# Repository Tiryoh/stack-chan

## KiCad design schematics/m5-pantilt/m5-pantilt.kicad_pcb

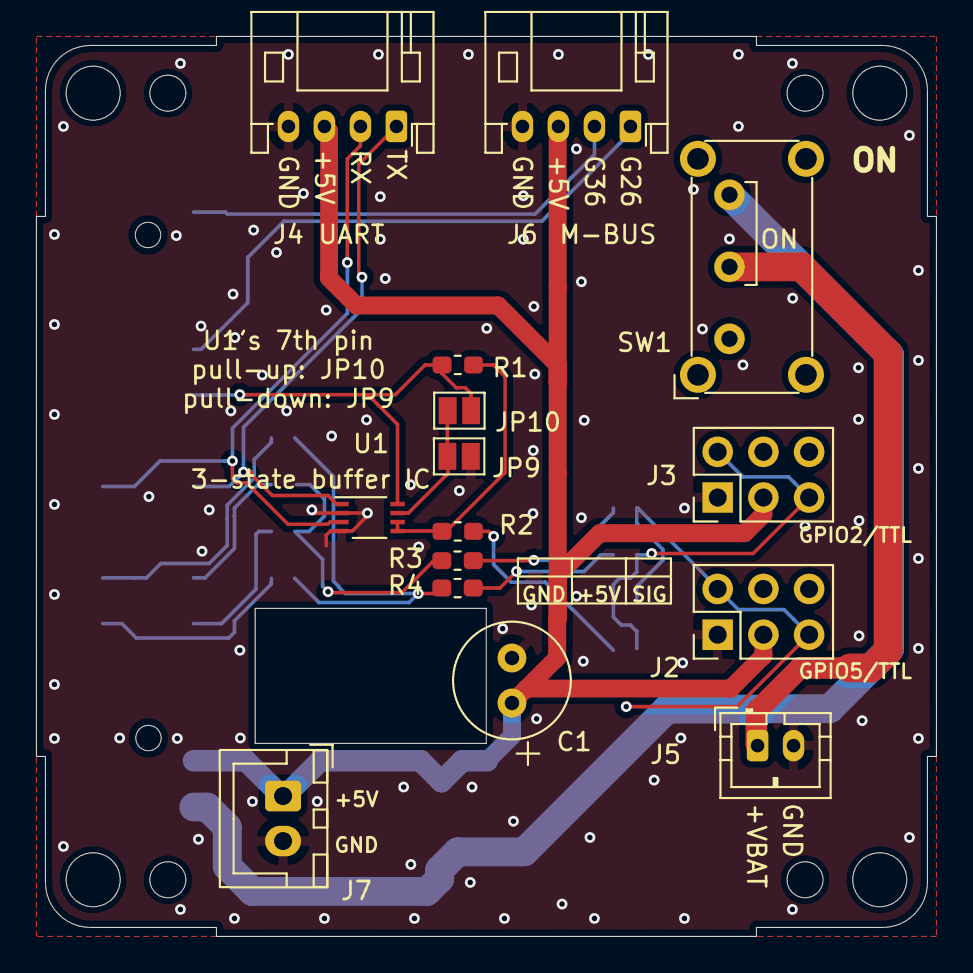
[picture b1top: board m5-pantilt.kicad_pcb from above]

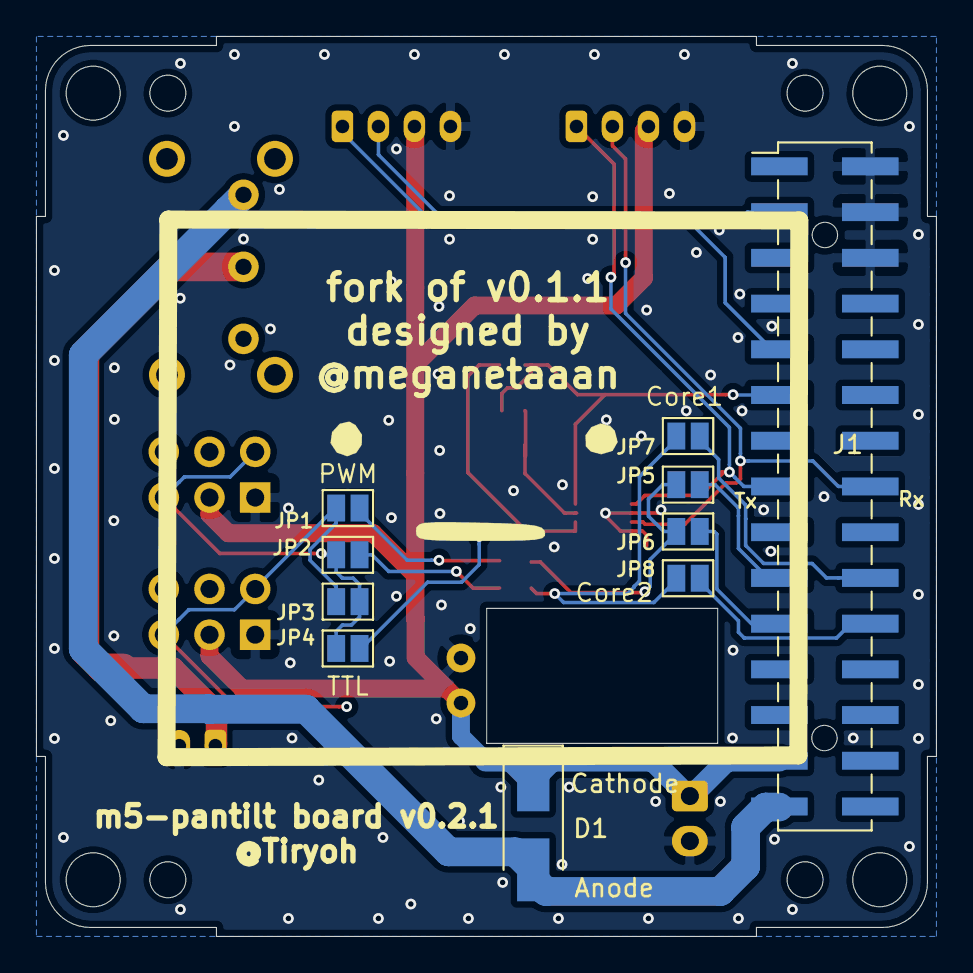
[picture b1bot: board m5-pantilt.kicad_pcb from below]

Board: 2 copper layers, 50.0 x 50.0 mm, 30 parts (11 on the bottom side), 22 nets.

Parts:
C1: 100u; C_Radial_D6.3mm_H11.0mm_P2.50mm
D1: D; D_SMA_Handsoldering
Hole1, Hole2, Hole3, Hole4: mountinghole_M2_M3
J1: Conn_02x15_Odd_Even; PinHeader_2x15_P2.54mm_Vertical_SMD
J2, J3: Conn_02x03_Odd_Even; PinHeader_2x03_P2.54mm_Vertical
J4, J6: Conn_01x04; JST_PH_S4B-PH-K_1x04_P2.00mm_Horizontal
J5: BAT; JST_PH_B2B-PH-K_1x02_P2.00mm_Vertical
J7: 5V_POWER; JST_XH_B2B-XH-A_1x02_P2.50mm_Vertical
JP1, JP2, JP3, JP4, JP5, JP6, JP7, JP8, JP9, JP10: Jumper_2_Open; SolderJumper-2_P1.3mm_Open_Pad1.0x1.5mm
LOGO: LOGO; avatar_small
R1, R3, R4: 1k; R_0603_1608Metric_Pad1.05x0.95mm_HandSolder
R2: 100; R_0603_1608Metric_Pad1.05x0.95mm_HandSolder
SW1: SW_SPDT; SW_E-Switch_EG1224_SPDT_Angled
U1: TC7WH241FK; NL27WZ125USG

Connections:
+3V3: J1.11, JP10.1, R1.1, U1.8
+5V: C1.2, D1.1, J1.27, J2.3, J3.3, J4.3, J6.3, J7.1
/PORTB1: J1.9, J6.1
/PORTB2: J1.3, J6.2
/PWM1: JP5.2, JP6.2, R3.2
/PWM1_C1: J1.19, JP5.1
/PWM1_C2: J1.21, JP6.1
/PWM2: JP7.2, JP8.2, R4.2
/PWM2_C1: J1.20, JP7.1
/PWM2_C2: J1.22, JP8.1
/RXD2: J1.16, J4.2, U1.3
/TXD2: J1.15, J4.1, U1.1
GND: C1.1, J1.2, J1.4, J1.6, J2.1, J3.1, J4.4, J5.2, J6.4, J7.2, JP9.1, U1.2, U1.4
unnamed: D1.2, J1.29, SW1.3
unnamed: J2.2, J2.5, JP1.2, JP3.1
unnamed: J3.2, J3.5, JP2.2, JP3.2, JP4.1
unnamed: J5.1, SW1.2
unnamed: JP1.1, R3.1
unnamed: JP2.1, R4.1
unnamed: JP4.2, R2.1
unnamed: JP9.2, JP10.2, U1.7
unnamed: R1.2, R2.2, U1.5, U1.6

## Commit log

2021-11-15 Update to v0.2.0
    Support another Three-State Bus Buffers, TC7WH241FK
2021-12-21 Update to v0.2.1
    Add description to schematic and PCB

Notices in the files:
parts and their libraries:
Copyright 2021 Accelerated Designs. All rights reserved.
